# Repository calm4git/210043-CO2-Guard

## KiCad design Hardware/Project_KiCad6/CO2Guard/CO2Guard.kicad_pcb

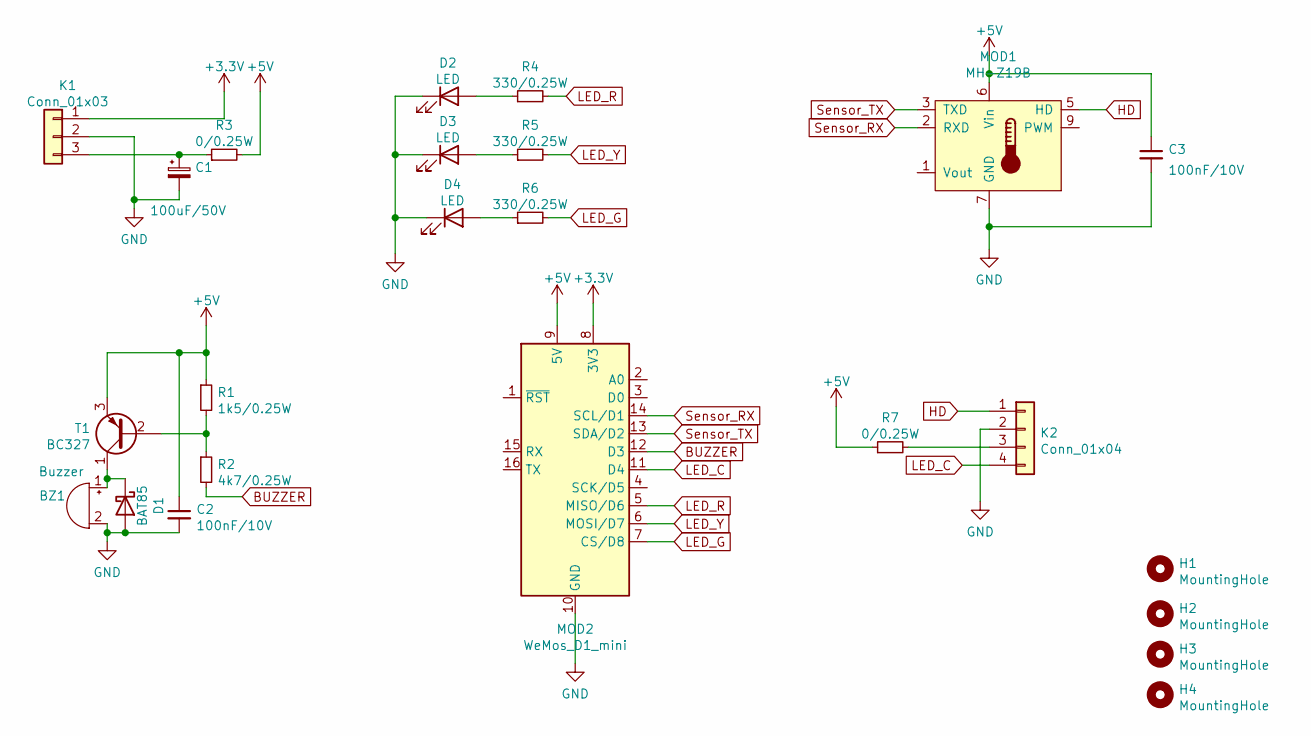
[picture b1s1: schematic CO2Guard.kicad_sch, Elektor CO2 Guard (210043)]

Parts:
BZ1: Buzzer; Buzzer_12x9.5RM7.6; mpn WT-1205
C1: 100uF/50V; CP_Radial_D6.3mm_P2.50mm; mpn 860020573008
C2, C3: 100nF/10V; C_Rect_L7.2mm_W2.5mm_P5.00mm_FKS2_FKP2_MKS2_MKP2; mpn MKS2C031001A00KSSD
D1: BAT85; D_DO-35_SOD27_P7.62mm_Horizontal; mpn BAT85S-TR
D2: LED; LED_D3.0mm; mpn 151031SS04000
D3: LED; LED_D3.0mm; mpn 151031YS06000
D4: LED; LED_D3.0mm; mpn 151031VS06000
H1, H2, H3, H4: MountingHole; MountingHole_3.2mm_M3
K1: Conn_01x03; PinSocket_1x03_P2.54mm_Vertical
K2: Conn_01x04; PinSocket_1x04_P2.54mm_Vertical
MOD1: MH-Z19B; Winsen_MH-Z19B
MOD2: WeMos_D1_mini; WEMOS_D1_mini_light
R1: 1k5/0.25W; R_Axial_DIN0207_L6.3mm_D2.5mm_P10.16mm_Horizontal; mpn LR0204F1K5
R2: 4k7/0.25W; R_Axial_DIN0207_L6.3mm_D2.5mm_P10.16mm_Horizontal; mpn CFR-25JB-52-4K7
R3: 0/0.25W; R_Axial_DIN0414_L11.9mm_D4.5mm_P15.24mm_Horizontal; mpn ZR0207C
R4, R5, R6: 330/0.25W; R_Axial_DIN0207_L6.3mm_D2.5mm_P10.16mm_Horizontal; mpn MBA02040C3300FRP00
R7: 0/0.25W; R_Axial_DIN0207_L6.3mm_D2.5mm_P10.16mm_Horizontal; mpn ZR0207C
T1: BC327; TO-92_Inline; mpn BC32725BU

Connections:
+3V3: K1.1, MOD2.8 (3V3)
+5V: C2.1, C3.1, MOD1.6 (Vin), MOD2.9 (5V), R1.1, R3.2, R7.1, T1.3 (E)
BUZZER: MOD2.12 (D3), R2.2
GND: BZ1.2 (+), C1.2, C2.2, C3.2, D1.2 (A), D2.1 (K), D3.1 (K), D4.1 (K), K1.2, K2.2, MOD1.7 (GND), MOD2.10 (GND)
HD: K2.1, MOD1.5 (HD)
LED_C: K2.4, MOD2.11 (D4)
LED_G: MOD2.7 (CS/D8), R6.2
LED_R: MOD2.5 (MISO/D6), R4.2
LED_Y: MOD2.6 (MOSI/D7), R5.2
unnamed: BZ1.1 (-), D1.1 (K), T1.1 (C)
unnamed: C1.1, K1.3, R3.1
unnamed: D2.2 (A), R4.1
unnamed: D3.2 (A), R5.1
unnamed: D4.2 (A), R6.1
unnamed: K2.3, R7.2
unnamed: R1.2, R2.1, T1.2 (B)
Sensor_RX: MOD1.2 (RXD), MOD2.14 (SCL/D1)
Sensor_TX: MOD1.3 (TXD), MOD2.13 (SDA/D2)

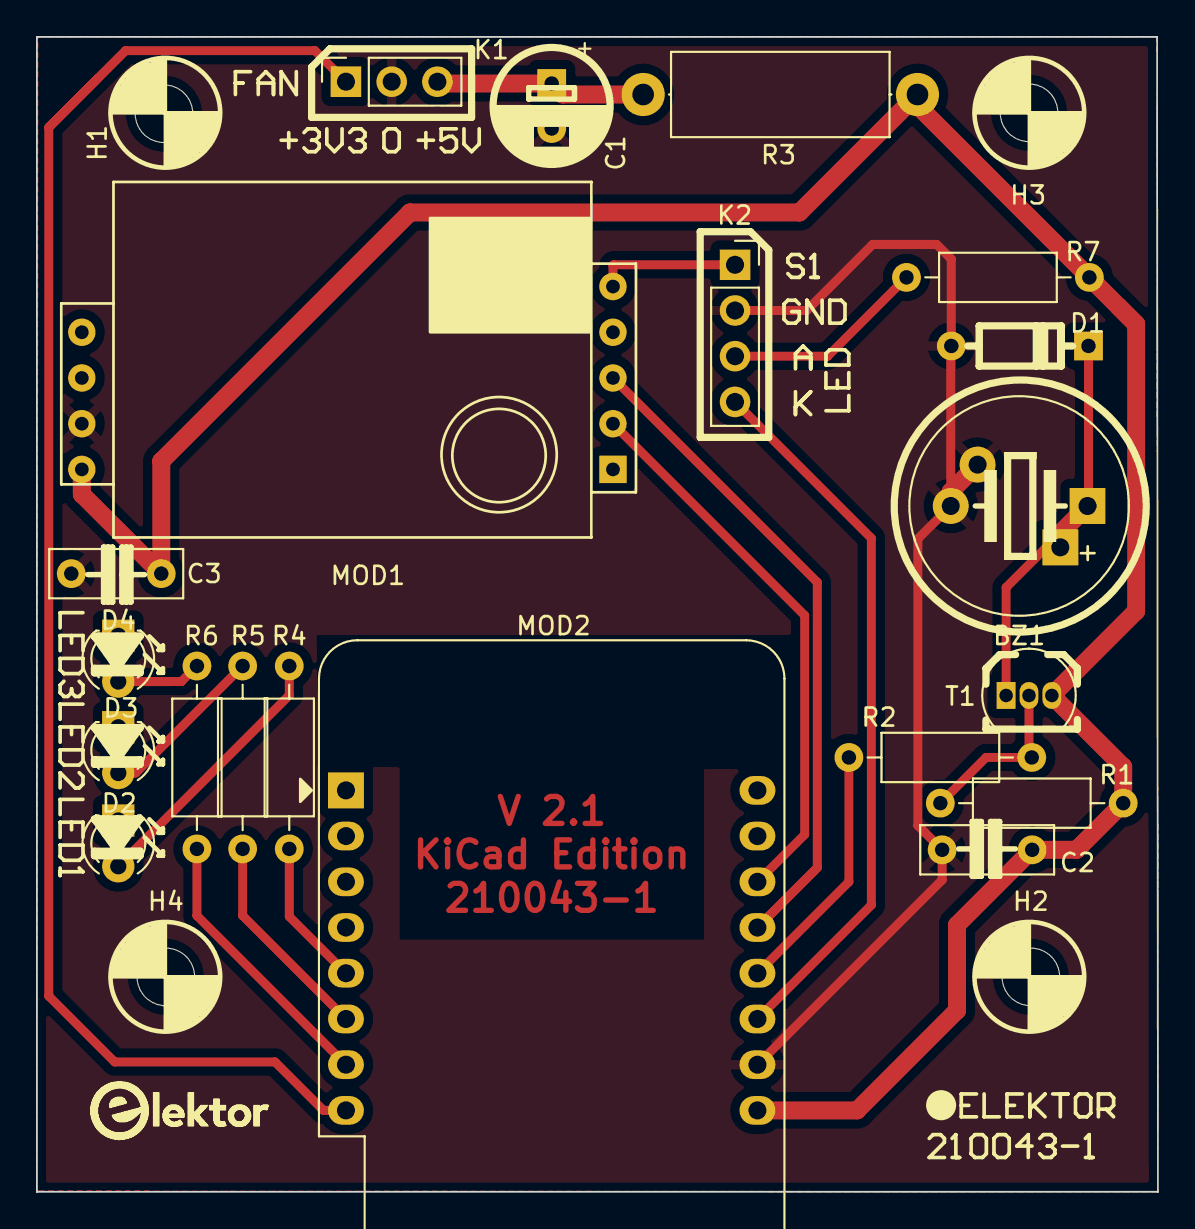
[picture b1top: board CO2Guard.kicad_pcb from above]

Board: 2 copper layers, 62.3 x 64.2 mm, 24 parts (0 on the bottom side), 18 nets.

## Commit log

2022-01-13 added MPN to schematic parts
2022-01-18 Added Enclosure
2022-05-07 NOTES save fixed
    Fixed a bug while wrtiting notes to EEPROM
2022-05-08 Update datastore.cpp
    Fixed some overlap in EEPROM of some structs
